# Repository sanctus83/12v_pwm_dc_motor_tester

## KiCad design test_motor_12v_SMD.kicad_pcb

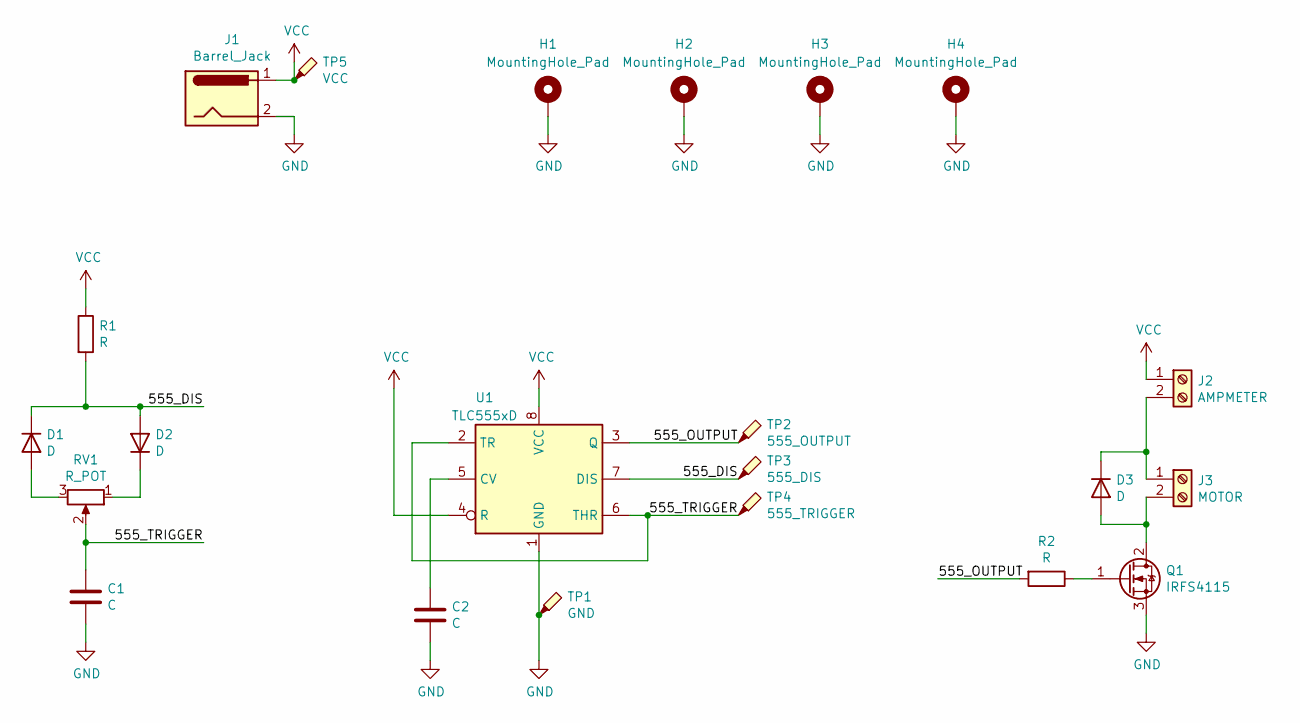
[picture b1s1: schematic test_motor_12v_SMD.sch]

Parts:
C1, C2: C; C_0805_2012Metric_Pad1.18x1.45mm_HandSolder
D1, D2, D3: D; D_0805_2012Metric_Pad1.15x1.40mm_HandSolder
H1, H2, H3, H4: MountingHole_Pad; MountingHole_3.2mm_M3_Pad_Via
J1: Barrel_Jack; BarrelJack_CUI_PJ-063AH_Horizontal
J2: AMPMETER; TerminalBlock_Phoenix_MKDS-1,5-2-5.08_1x02_P5.08mm_Horizont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
J3: MOTOR; TerminalBlock_Phoenix_MKDS-1,5-2-5.08_1x02_P5.08mm_Horizont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
Q1: IRFS4115; TO-263-2
R1, R2: R; R_0805_2012Metric_Pad1.20x1.40mm_HandSolder
RV1: R_POT; Potentiometer_Bourns_3266W_Vertical
TP1: GND; PinHeader_1x01_P2.54mm_Vertical
TP2: 555_OUTPUT; PinHeader_1x01_P2.54mm_Vertical
TP3: 555_DIS; PinHeader_1x01_P2.54mm_Vertical
TP4: 555_TRIGGER; PinHeader_1x01_P2.54mm_Vertical
TP5: VCC; PinHeader_1x01_P2.54mm_Vertical
U1: TLC555xD; SOIC-8_3.9x4.9mm_P1.27mm

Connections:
/555_DIS: D1.1 (K), D2.2 (A), R1.2, TP3.1, U1.7 (DIS)
/555_OUTPUT: R2.2, TP2.1, U1.3 (Q)
/555_TRIGGER: C1.1, RV1.2, TP4.1, U1.2 (TR), U1.6 (THR)
GND: C1.2, C2.2, H1.1, H2.1, H3.1, H4.1, J1.2, Q1.3 (S), TP1.1, U1.1 (GND)
unnamed: C2.1, U1.5 (CV)
unnamed: D1.2 (A), RV1.3
unnamed: D2.1 (K), RV1.1
unnamed: D3.1 (K), J2.2, J3.1
unnamed: D3.2 (A), J3.2, Q1.2 (D)
unnamed: Q1.1 (G), R2.1
VCC: J1.1, J2.1, R1.1, TP5.1, U1.4 (R), U1.8 (VCC)

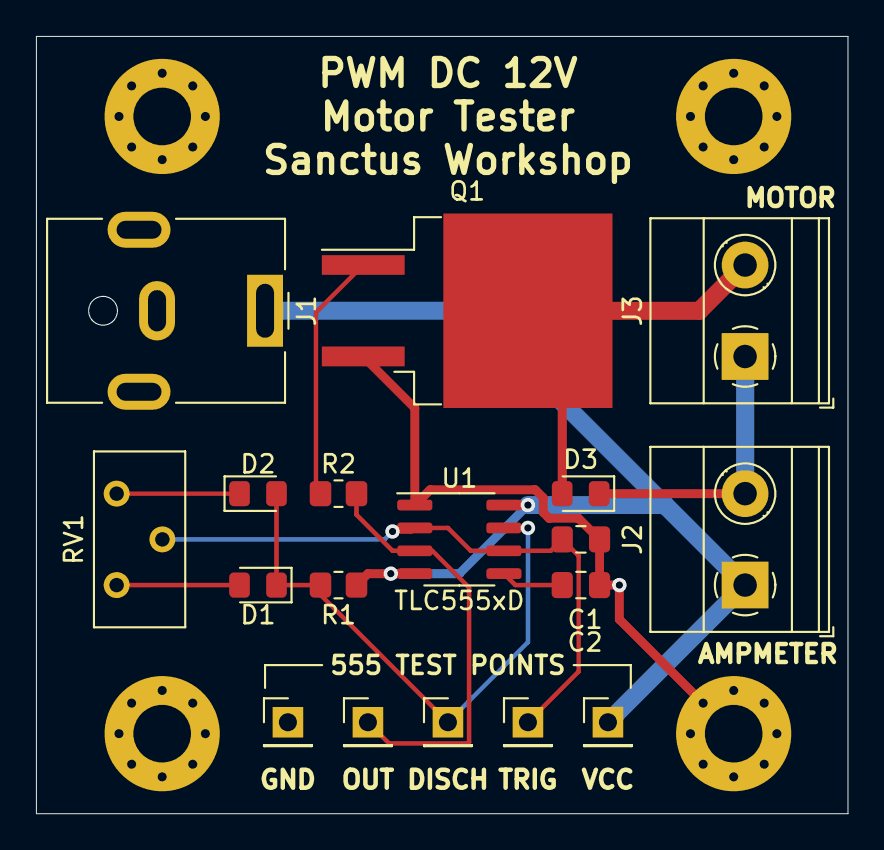
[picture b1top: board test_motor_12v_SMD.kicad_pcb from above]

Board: 2 copper layers, 45.1 x 43.2 mm, 22 parts (0 on the bottom side), 11 nets.
